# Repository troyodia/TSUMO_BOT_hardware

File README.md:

# TSUMO_BOT_hardware

This repository contains the schematic and PCB designs for TSUMO_BOT a sumo robot (12x12cm), created in KiCad and manufactured by JLCPCB. The PCB is a 4-layer board, with an STM32L476RG microcontroller, two motor drivers TB6612FNG, an IR reciever TSP382, MOSFET circuit protection FDS6687, a 5V buck converter RT8259, a 3.3V regulator AMS1117, a 5V power mux TPS2116DRL and a USB-C connector with ESD protection (USBLC6).

## Setup

First clone the repo:

```
git clone https://github.com/troyodia/TSUMO_BOT_hardware.git
```

Import the project into KiCad 9.0 and make sure you have the "default global symbol library table" and the "default footprint library" available. KiCad should find the 3Dmodels and symbols under libs/ automatically. You must manually import the footprints under libs/footprints/ (select "file/add library" from the menu in the footprint editor and add them to the project).

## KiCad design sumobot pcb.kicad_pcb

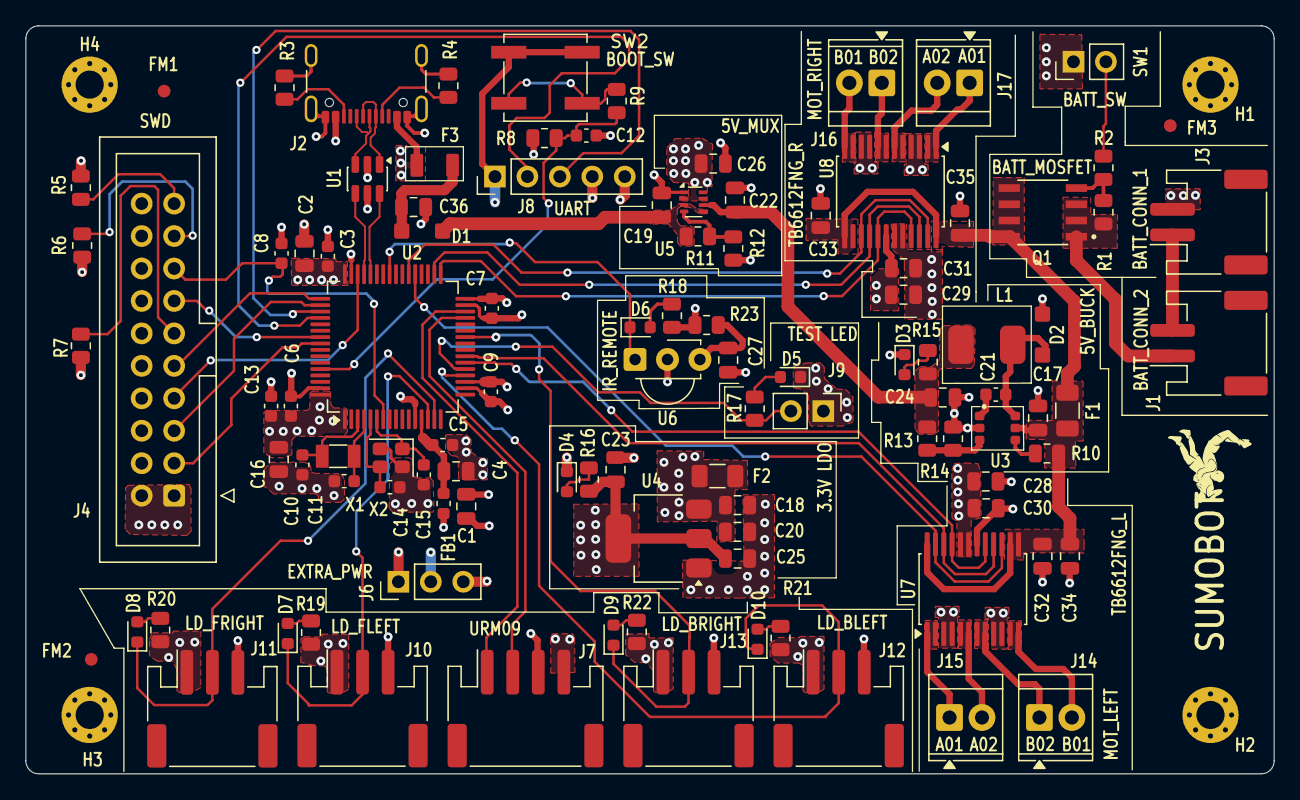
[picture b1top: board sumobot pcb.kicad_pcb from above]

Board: 4 copper layers, 97.7 x 58.5 mm, 110 parts (0 on the bottom side), 72 nets.

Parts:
C1, C2, C4, C27: 1u; C_0805_2012Metric
C3, C6, C7, C8, C9, C12, C13: 100n; C_0603_1608Metric
C5, C21: 10n; C_0603_1608Metric
C10, C11: 8.2p; C_0603_1608Metric
C14, C15: 15p; C_0603_1608Metric
C16: 4u7; C_0805_2012Metric
C17, C19, C22, C26, C30, C31, C34, C35: 10u; C_0805_2012Metric
C18, C24, C25: 22u; C_0805_2012Metric
C20, C23, C28, C29, C32, C33, C36: 0.1u; C_0805_2012Metric
D1, D2: B5819W; B5819W SOD123
D3, D4, D6, D7, D8, D9, D10: RED_LED; LED_0603_1608Metric
D5: WHITE_LED; LED_0603_1608Metric
F1, F2: 750mA; Fuse_1206_3216Metric
F3: 1206L110TH1; 1206L110THYR_SMT
FB1: 120R; L_0603_1608Metric
FM1, FM2, FM3: Fiducial; Fiducial_1mm_Mask2mm
H1, H2, H3, H4: MountingHole_Pad; MountingHole_2.2mm_M2_Pad_Via
J1: BATT1_CONN; JST_PH_S2B-PH-SM4-TB_1x02-1MP_P2.00mm_Horizontal
J2: USB_C_Receptacle_USB2.0_16P; USB_C_Receptacle_GCT_USB4105-xx-A_16P_TopMnt_Horizontal
J3: BATT2_CONN; JST_PH_S2B-PH-SM4-TB_1x02-1MP_P2.00mm_Horizontal
J4: Conn_ARM_JTAG_SWD_20; IDC-Header_2x10_P2.54mm_Vertical
J6: EXTRA PWR_PINS; PinHeader_1x03_P2.54mm_Vertical
J7: URM09_CONN; JST_PH_S4B-PH-SM4-TB_1x04-1MP_P2.00mm_Horizontal
J8: UART_CONN; PinHeader_1x05_P2.54mm_Vertical
J9: TEST_LED_PINS; PinHeader_1x02_P2.54mm_Vertical
J10: LD_FRONT_LEFT_CONN; JST_PH_S3B-PH-SM4-TB_1x03-1MP_P2.00mm_Horizontal
J11: LD_FRONT_RIGHT_CONN; JST_PH_S3B-PH-SM4-TB_1x03-1MP_P2.00mm_Horizontal
J12: LD_BACK_LEFT_CONN; JST_PH_S3B-PH-SM4-TB_1x03-1MP_P2.00mm_Horizontal
J13: LD_BACK_RIGHT_CONN; JST_PH_S3B-PH-SM4-TB_1x03-1MP_P2.00mm_Horizontal
J14: MOTOR_LEFT_FRONT_CONN; TerminalBlock_TE_282834-2_1x02_P2.54mm_Horizontal
J15: MOTOR_LEFT_BACK_CONN; TerminalBlock_TE_282834-2_1x02_P2.54mm_Horizontal
J16: MOTOR_RIGHT_FRONT_CONN; TerminalBlock_TE_282834-2_1x02_P2.54mm_Horizontal
J17: MOTOR_RIGHT_BACK_CONN; TerminalBlock_TE_282834-2_1x02_P2.54mm_Horizontal
L1: 6.8uH; MWSA0518S-6R8MT
Q1: FDS6681Z; FDS6681Z_Footprint
R1, R10: 100k; R_0805_2012Metric
R2, R5, R6, R7, R8, R12: 10K; R_0805_2012Metric
R3, R4: 5K1; R_0805_2012Metric
R9, R17, R18: 220R; R_0805_2012Metric
R11: 33K; R_0805_2012Metric
R13: 62k; R_0805_2012Metric
R14: 12k; R_0805_2012Metric
R15, R16: 1K; R_0805_2012Metric
R19, R20, R21, R22, R23: 470R; R_0805_2012Metric
SW1: SW_SPST; PinHeader_1x02_P2.54mm_Vertical
SW2: SW_Push; SW_SPST_B3SL-1002P
U1: USBLC6-2SC6; SOT-23-6
U2: STM32L476RGT6; LQFP-64_10x10mm_P0.5mm
U3: RT8259; RT8259GE_RT8259GE SOT-23-6 Surface Mount
U4: AMS1117-3.3; SOT-223-3_TabPin2
U5: TPS2116DRL; SOT-583-8
U6: TSOP382xx; Vishay_MINICAST-3Pin
U7, U8: TB6612FNG; SSOP-24_5.3x8.2mm_P0.65mm
X1: 32KHz768; Crystal_SMD_3215-2Pin_3.2x1.5mm
X2: 16MHz; Crystal_SMD_2520-4Pin_2.5x2.0mm

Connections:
+3.3V: C1.1, C2.1, C3.1, C6.1, C7.1, C9.1, C13.1, C16.1, C23.1, C25.1, C28.1, C29.1, C30.1, C31.1, FB1.1, J4.1 (VTREF), J4.2 (VCC/NC), J6.2, J8.1, R16.1, R18.2, R23.2, SW2.2, U2.1 (VBAT), U2.19 (VDD), U2.32 (VDD), U2.48 (VDDUSB), U2.64 (VDD), U4.2 (VO), U7.19 (STBY), U7.20 (VCC), U8.19 (STBY), U8.20 (VCC)
+PWR_5V: C18.1, C20.1, C26.1, F2.1, F2.2, J6.3, J7.4, J8.5, J10.1, J11.1, J12.1, J13.1, R19.1, R20.1, R21.1, R22.1, U4.3 (VI), U5.2 (VOUT), U5.7 (VOUT)
+VBATT: C17.1, C32.1, C33.1, C34.1, C35.1, F1.1, F1.2, Q1.5 (D), Q1.6 (D), Q1.7 (D), Q1.8 (D), R10.1, U3.5 (VIN), U7.13 (VM2), U7.14 (VM3), U7.24 (VM1), U8.13 (VM2), U8.14 (VM3), U8.24 (VM1)
+VBATT_5V: C22.1, C24.1, L1.2, R13.1, R15.1, U5.6 (VIN2)
+VBUS_5V: C19.1, D1.1 (K), R11.1, U5.3 (VIN1), U5.5 (MODE)
/+3.3VA: C4.1, C5.1, FB1.2, U2.13 (VDDA)
/BATT12_TIE: J1.2, J3.1
/BOOT0: C12.1, R8.1, R9.1, U2.60 (BOOT0)
/GATE_IN: Q1.4 (G), R1.2, R2.1
/HSE_IN: C14.1, U2.5 (PH0), X2.3
/HSE_OUT: C15.1, U2.6 (PH1), X2.1
/LED_D3_A: D3.2 (A), R15.2
/LED_D4_A: D4.2 (A), R16.2
/LSE_IN: C10.1, U2.3 (PC14), X1.2
/LSE_OUT: C11.1, U2.4 (PC15), X1.1
/NRST: C8.1, J4.15 (~SRST), U2.7 (NRST)
/PR1_IN: R11.2, R12.1, U5.4 (PR1)
/RT8_BOOT: C21.2, U3.1 (BOOT)
/RT8_EN: R10.2, U3.4 (EN)
/RT8_FB: R13.2, R14.1, U3.3 (FB)
/RT8_PHASE: C21.1, D2.1 (K), L1.1, U3.6 (PHASE)
/SCH_D1_A: C36.1, D1.2 (A), F3.2
/SW1_TERM2: R2.2, SW1.2 (B)
/SW2_TERM1: R9.2, SW2.1
/SWDC_DBGACK: J4.19 (DBGACK/NC), R5.1
/SWDC_DBGRQ: J4.17 (DBGRQ/NC), R6.1
/SWDC_RTCK: J4.11 (RTCK), R7.1
/Sumo sensors and Motors/LED_D5_A: D5.2 (A), R17.2
/Sumo sensors and Motors/LED_D6_A: D6.2 (A), R18.1
/Sumo sensors and Motors/LED_D7_A: D7.2 (A), R19.2
/Sumo sensors and Motors/LED_D8_A: D8.2 (A), R20.2
/Sumo sensors and Motors/LED_D9_A: D10.2 (A), R21.2
/Sumo sensors and Motors/LED_D10_A: D9.2 (A), R22.2
/Sumo sensors and Motors/TSOP_VS_3.3: C27.1, R23.1, U6.3 (Vs)
/USBC_CC1: J2.A5 (CC1), R4.1
/USBC_CC2: J2.B5 (CC2), R3.1
/USBC_D+: J2.A6 (D+), J2.B6 (D+), U1.3 (I/O2)
/USBC_D-: J2.A7 (D-), J2.B7 (D-), U1.1 (I/O1)
/VBATT: J1.1, Q1.1 (S), Q1.2 (S), Q1.3 (S), R1.1
/VBUS: F3.1, J2.A4 (VBUS), J2.A9 (VBUS), J2.B4 (VBUS), J2.B9 (VBUS), U1.5 (VBUS)
GND: C1.2, C2.2, C3.2, C4.2, C5.2, C6.2, C7.2, C8.2, C9.2, C10.2, C11.2, C12.2, C13.2, C14.2, C15.2, C16.2, C17.2, C18.2, C19.2, C20.2, C22.2, C23.2, C24.2, C25.2, C26.2, C27.2, C28.2, C29.2, C30.2, C31.2, C32.2, C33.2, C34.2, C35.2, C36.2, D2.2 (A), D3.1 (K), D4.1 (K), D5.1 (K), H1.1, H2.1, H3.1, H4.1, J2.A1 (GND), J2.A12 (GND), J2.B1 (GND), J2.B12 (GND), J2.S1 (SHIELD), J3.2, J4.4 (GND), J4.6 (GND), J4.8 (GND), J4.10 (GND), J4.12 (GND), J4.14 (GND), J4.16 (GND), J4.18 (GND), J4.20 (GND), J6.1, J7.3, J8.4, J9.1, J10.3, J11.3, J12.3, J13.3, R3.2, R4.2, R5.2, R6.2, R7.2, R8.2, R12.2, R14.2, SW1.1 (A), U1.2 (GND), U2.12 (VSSA), U2.18 (VSS), U2.31 (VSS), U2.47 (VSS), U2.63 (VSS), U3.2 (GND), U4.1 (GND), U5.1 (GND), U6.2 (GND), U7.3 (PGND1), U7.4 (PGND1), U7.9 (PGND2), U7.10 (PGND2), U7.18 (GND), U8.3 (PGND1), U8.4 (PGND1), U8.9 (PGND2), U8.10 (PGND2), U8.18 (GND), X2.2, X2.4
IR_REMOTE: D6.1 (K), U2.41 (PA8), U6.1 (OUT)
LD_BACK_LEFT: D10.1 (K), J12.2, U2.20 (PA4)
LD_BACK_RIGHT: D9.1 (K), J13.2, U2.26 (PB0)
LD_FRONT_LEFT: D7.1 (K), J10.2, U2.14 (PA0)
LD_FRONT_RIGHT: D8.1 (K), J11.2, U2.15 (PA1)
ML_BACK_B01: J14.2, U7.11 (BO1), U7.12 (BO1)
ML_BACK_B02: J14.1, U7.7 (BO2), U7.8 (BO2)
ML_FRONT_AO1: J15.1, U7.1 (AO1), U7.2 (AO1)
ML_FRONT_AO2: J15.2, U7.5 (AO2), U7.6 (AO2)
MOTOR_LEFT_CH1: U2.22 (PA6), U7.17 (BIN1), U7.21 (AIN1)
MOTOR_LEFT_CH2: U2.23 (PA7), U7.16 (BIN2), U7.22 (AIN2)
MOTOR_PWM_LEFT: U2.37 (PC6), U7.15 (PWMB), U7.23 (PWMA)
MOTOR_PWM_RIGHT: U2.38 (PC7), U8.15 (PWMB), U8.23 (PWMA)
MOTOR_RIGHT_CH1: U2.33 (PB12), U8.17 (BIN1), U8.21 (AIN1)
MOTOR_RIGHT_CH2: U2.34 (PB13), U8.16 (BIN2), U8.22 (AIN2)
MR_BACK_A01: J17.1, U8.1 (AO1), U8.2 (AO1)
MR_BACK_A02: J17.2, U8.5 (AO2), U8.6 (AO2)
MR_FRONT_BO1: J16.2, U8.11 (BO1), U8.12 (BO1)
MR_FRONT_BO2: J16.1, U8.7 (BO2), U8.8 (BO2)
SCL: J7.2, U2.29 (PB10)
SDA: J7.1, U2.30 (PB11)
SWD_CLK: J4.9 (TCK/SWCLK), U2.49 (PA14)
SWD_DIO: J4.7 (TMS/SWDIO), U2.46 (PA13)
SWD_TDI: J4.5 (TDI), U2.50 (PA15)
SWD_TDO: J4.13 (TDO/SWO), U2.55 (PB3)
SWD_TRST: J4.3 (~TRST), U2.56 (PB4)
TEST LED: J9.2, R17.1, U2.21 (PA5)
UART_RX: J8.2, U2.52 (PC11)
UART_TX: J8.3, U2.51 (PC10)
USB_D+: U1.4 (I/O2), U2.45 (PA12)
USB_D-: U1.6 (I/O1), U2.44 (PA11)

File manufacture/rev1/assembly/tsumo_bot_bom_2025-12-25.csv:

Reference,Qty,Value,Exclude from BOM,Footprint,Datasheet,LCSC
X2,1,16MHz,,Crystal:Crystal_SMD_2520-4Pin_2.5x2.0mm,~,C7270509
X1,1,32KHz768,,Crystal:Crystal_SMD_3215-2Pin_3.2x1.5mm,~, C5633029
U5,1,TPS2116DRL,,Package_TO_SOT_SMD:SOT-583-8,https://www.ti.com/lit/ds/symlink/tps2116.pdf,C3235557
J2,1,USB_C_Receptacle_USB2.0_16P,,Connector_USB:USB_C_Receptacle_GCT_USB4105-xx-A_16P_TopMnt_Horizontal,https://www.usb.org/sites/default/files/documents/usb_type-c.zip,C3020560
"C10,C11",2,8.2p,,Capacitor_SMD:C_0603_1608Metric,~,C1322360
"C17,C19,C22,C26,C30,C31,C34,C35",8,10u,,Capacitor_SMD:C_0805_2012Metric,~,C440198
L1,1,6.8uH,,MWSA0518S-6R8MT:MWSA0518S-6R8MT,https://mm.digikey.com/Volume0/opasdata/d220001/medias/docus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, C408348
SW2,1,SW_Push,,Button_Switch_SMD:SW_SPST_B3SL-1002P,~, C306880
J3,1,BATT2_CONN,,Connector_JST:JST_PH_S2B-PH-SM4-TB_1x02-1MP_P2.00mm_Horizontal,~, C295747
J1,1,BATT1_CONN,,Connector_JST:JST_PH_S2B-PH-SM4-TB_1x02-1MP_P2.00mm_Horizontal,~, C295747
J7,1,URM09_CONN,,Connector_JST:JST_PH_S4B-PH-SM4-TB_1x04-1MP_P2.00mm_Horizontal,~,C265332
J13,1,LD_BACK_RIGHT_CONN,,Connector_JST:JST_PH_S3B-PH-SM4-TB_1x03-1MP_P2.00mm_Horizontal,~,C265101
J12,1,LD_BACK_LEFT_CONN,,Connector_JST:JST_PH_S3B-PH-SM4-TB_1x03-1MP_P2.00mm_Horizontal,~,C265101
J11,1,LD_FRONT_RIGHT_CONN,,Connector_JST:JST_PH_S3B-PH-SM4-TB_1x03-1MP_P2.00mm_Horizontal,~,C265101
J10,1,LD_FRONT_LEFT_CONN,,Connector_JST:JST_PH_S3B-PH-SM4-TB_1x03-1MP_P2.00mm_Horizontal,~,C265101
Q1,1,FDS6681Z,,FDS6681Z:FDS6681Z_Footprint,https://jlcpcb.com/api/file/downloadByFileSystemAccessId/858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,C236906
"F1,F2",2,750mA,,Fuse:Fuse_1206_3216Metric,~,C187594
R13,1,62k,,Resistor_SMD:R_0805_2012Metric,~,C178156
"R1,R10",2,100k,,Resistor_SMD:R_0805_2012Metric,~,C149504
"U7,U8",2,TB6612FNG,,Package_SO:SSOP-24_5.3x8.2mm_P0.65mm,https://toshiba.semicon-storage.com/us/product/linear/motord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,C141517
F3,1,1206L110TH1,,1206L110TH1_SMT:1206L110THYR_SMT,https://jlcpcb.com/api/file/downloadByFileSystemAccessId/858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,C126818
U2,1,STM32L476RGT6,,Package_QFP:LQFP-64_10x10mm_P0.5mm,https://www.st.com/resource/en/datasheet/stm32l476rg.pdf,C74797
"C5,C21",2,10n,,Capacitor_SMD:C_0603_1608Metric,~,C57112
"C18,C24,C25",3,22u,,Capacitor_SMD:C_0805_2012Metric,~,C45783
"C1,C2,C4,C27",4,1u,,Capacitor_SMD:C_0805_2012Metric,~,C28323
"R3,R4",2,5K1,,Resistor_SMD:R_0805_2012Metric,,C27834
"R19,R20,R21,R22,R23",5,470R,,Resistor_SMD:R_0805_2012Metric,~,C17710
R11,1,33K,,Resistor_SMD:R_0805_2012Metric,,C17633
"R9,R17,R18",3,220R,,Resistor_SMD:R_0805_2012Metric,~,C17557
"R15,R16",2,1K,,Resistor_SMD:R_0805_2012Metric,,C17513
R14,1,12k,,Resistor_SMD:R_0805_2012Metric,~,C17444
"R2,R5,R6,R7,R8,R12",6,10K,,Resistor_SMD:R_0805_2012Metric,,C17414
U3,1,RT8259,,RT8259GE:RT8259GE_RT8259GE SOT-23-6 Surface Mount,https://www.richtek.com/SaveDownload.aspx?specid=RT8259, C16819
FB1,1,120R,,Inductor_SMD:L_0603_1608Metric,~,C14709
"C3,C6,C7,C8,C9,C12,C13",7,100n,,Capacitor_SMD:C_0603_1608Metric,~,C14663
"D1,D2",2,B5819W,,Schottky Diode Custom:B5819W SOD123,https://jlcpcb.com/api/file/downloadByFileSystemAccessId/858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,C8598
U1,1,USBLC6-2SC6,,Package_TO_SOT_SMD:SOT-23-6,https://www.st.com/resource/en/datasheet/usblc6-2.pdf,C7519
U4,1,AMS1117-3.3,,Package_TO_SOT_SMD:SOT-223-3_TabPin2,http://www.advanced-monolithic.com/pdf/ds1117.pdf,C6186
D5,1,WHITE_LED,,LED_SMD:LED_0603_1608Metric,~,C2290
"D3,D4,D6,D7,D8,D9,D10",7,RED_LED,,LED_SMD:LED_0603_1608Metric,~,C2286
C16,1,4u7,,Capacitor_SMD:C_0805_2012Metric,~,C1779
"C20,C23,C28,C29,C32,C33,C36",7,0.1u,,Capacitor_SMD:C_0805_2012Metric,~,C1711
"C14,C15",2,15p,,Capacitor_SMD:C_0603_1608Metric,~,C1644
U6,1,TSOP382xx,Excluded from BOM,OptoDevice:Vishay_MINICAST-3Pin,http://www.vishay.com/docs/82491/tsop382.pdf,
SW1,1,SW_SPST,Excluded from BOM,Connector_PinHeader_2.54mm:PinHeader_1x02_P2.54mm_Vertical,~,
J17,1,MOTOR_RIGHT_BACK_CONN,Excluded from BOM,TerminalBlock_TE-Connectivity:TerminalBlock_TE_282834-2_1x02_P2.54mm_Horizontal,~,
J16,1,MOTOR_RIGHT_FRONT_CONN,Excluded from BOM,TerminalBlock_TE-Connectivity:TerminalBlock_TE_282834-2_1x02_P2.54mm_Horizontal,~,
J15,1,MOTOR_LEFT_BACK_CONN,Excluded from BOM,TerminalBlock_TE-Connectivity:TerminalBlock_TE_282834-2_1x02_P2.54mm_Horizontal,~,
J14,1,MOTOR_LEFT_FRONT_CONN,Excluded from BOM,TerminalBlock_TE-Connectivity:TerminalBlock_TE_282834-2_1x02_P2.54mm_Horizontal,~,
J9,1,TEST_LED_PINS,Excluded from BOM,Connector_PinHeader_2.54mm:PinHeader_1x02_P2.54mm_Vertical,~,
J8,1,UART_CONN,Excluded from BOM,Connector_PinHeader_2.54mm:PinHeader_1x05_P2.54mm_Vertical,~,
J6,1,EXTRA PWR_PINS,Excluded from BOM,Connector_PinHeader_2.54mm:PinHeader_1x03_P2.54mm_Vertical,~,
J4,1,Conn_ARM_JTAG_SWD_20,Excluded from BOM,Connector_IDC:IDC-Header_2x10_P2.54mm_Vertical,http://infocenter.arm.com/help/topic/com.arm.doc.dui0499b/DU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,
"H1,H2,H3,H4",4,MountingHole_Pad,Excluded from BOM,MountingHole:MountingHole_2.2mm_M2_Pad_Via,~,
"FM1,FM2,FM3",3,Fiducial,Excluded from BOM,Fiducial:Fiducial_1mm_Mask2mm,~,

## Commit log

2026-01-02 Initial folder structure.
2026-01-02 uploaded manufacturing files for rev1 of pcb
2026-01-02 uploaded library files for rev1 of pcb
2026-01-02 uploaded images and created readme file
2026-01-02 fix readme
2026-01-07 added physical pcb image
2026-01-12 Updated PCB images
